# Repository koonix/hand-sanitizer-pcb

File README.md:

# Hand Sanitizer

Schematics and PCB of an automatic hand sanitizer dispenser. 

The firmware for the microcontroller is here: [hand-sanitizer-firmware](https://github.com/soystemd/hand-sanitizer-firmware)

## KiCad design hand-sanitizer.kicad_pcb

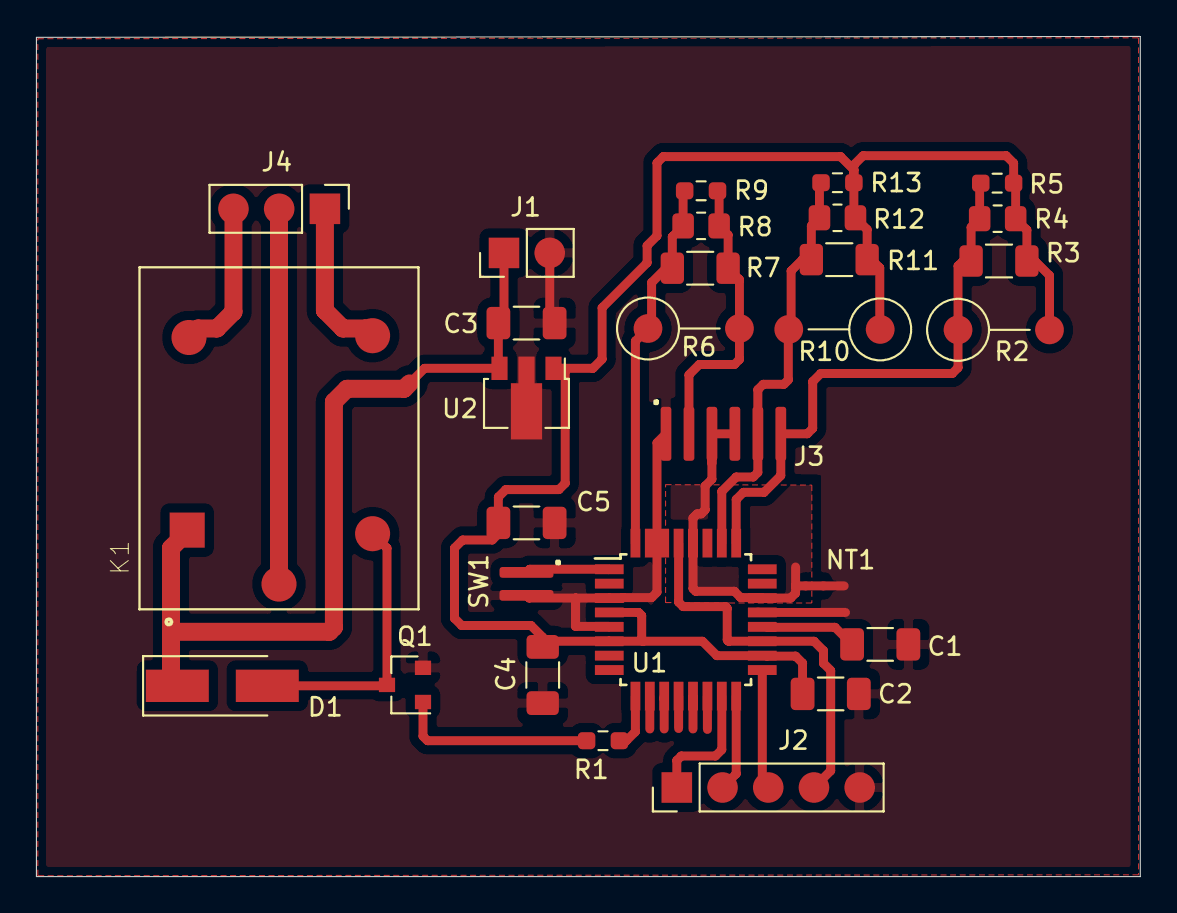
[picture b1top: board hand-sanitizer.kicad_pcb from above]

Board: 2 copper layers, 61.3 x 46.7 mm, 29 parts (0 on the bottom side), 20 nets.

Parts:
C1, C2, C3, C4, C5: 100n; C_1206_3216Metric_Pad1.33x1.80mm_HandSolder
D1: 1N4007; D_SMA_Handsoldering
J1: Conn_01x02; PinHeader_1x02_P2.54mm_Vertical
J2: prog; PinHeader_1x05_P2.54mm_Vertical
J3: Conn_01x06; Ribbon_6
J4: relay_terminal_out; PinHeader_1x03_P2.54mm_Vertical
K1: Milon-Relay
NT1: Net-Tie_2; NetTie-2_SMD_Pad0.5mm
Q1: MMBT2222; SOT-23
R1: 1K; R_0603_1608Metric_Pad0.98x0.95mm_HandSolder
R2, R6, R10: dip_var; R_Axial_DIN0309_L9.0mm_D3.2mm_P5.08mm_Vertical
R3, R7, R11: 1206_var; R_1206_3216Metric_Pad1.30x1.75mm_HandSolder
R4, R8, R12: 0805_var; R_0805_2012Metric_Pad1.20x1.40mm_HandSolder
R5, R9, R13: 0603_var; R_0603_1608Metric_Pad0.98x0.95mm_HandSolder
SW1: SW_Push; Ribbon_2
U1: ATmega8A-AU; TQFP-32_7x7mm_P0.8mm
U2: L78L05_SOT89; SOT-89-3

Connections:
+12V: C3.2, D1.1, J1.1, K1.A1, U2.3
/irled: R6.1, R7.1, R8.1, R9.1, U1.32
/mcu_button_pin: SW1.1, U1.1
/miso: J2.2, U1.16
/mosi: J2.1, U1.15
/photoResistor: J3.5, R10.2, R11.2, R12.2, R13.2, U1.26
/photoTransistor: J3.6, R2.1, R3.1, R4.1, R5.1, U1.25
/relay: R1.2, U1.9
/reset: J2.4, U1.19, U1.29
/ribbon_led: J3.2, R6.2, R7.2, R8.2, R9.2
/sck: J2.3, U1.17
GND: C1.2, C2.2, C3.1, C4.1, C5.1, J1.2, J2.5, J3.1, NT1.2, Q1.2, SW1.2, U1.3, U1.5, U1.21, U1.30, U1.31, U2.2
GNDA: J3.3, J3.4, NT1.1, U1.22, U1.28
unnamed: C1.1, U1.20
unnamed: D1.2, K1.A2, Q1.3
unnamed: J4.1, K1.NO
unnamed: J4.2, K1.COM
unnamed: J4.3, K1.NC
unnamed: Q1.1, R1.1
VCC: C2.1, C4.2, C5.2, R2.2, R3.2, R4.2, R5.2, R10.1, R11.1, R12.1, R13.1, U1.4, U1.6, U1.18, U2.1

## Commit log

2020-11-04 Initial template commit, added .gitignore
2020-11-24 Plot-temp is now the ignored plot directory.
2020-11-24 First pcb and schematics revision complete
2020-11-24 Nothing important changed
2020-11-24 Minor changes to pcb
2020-11-24 Added README and pcb.png
